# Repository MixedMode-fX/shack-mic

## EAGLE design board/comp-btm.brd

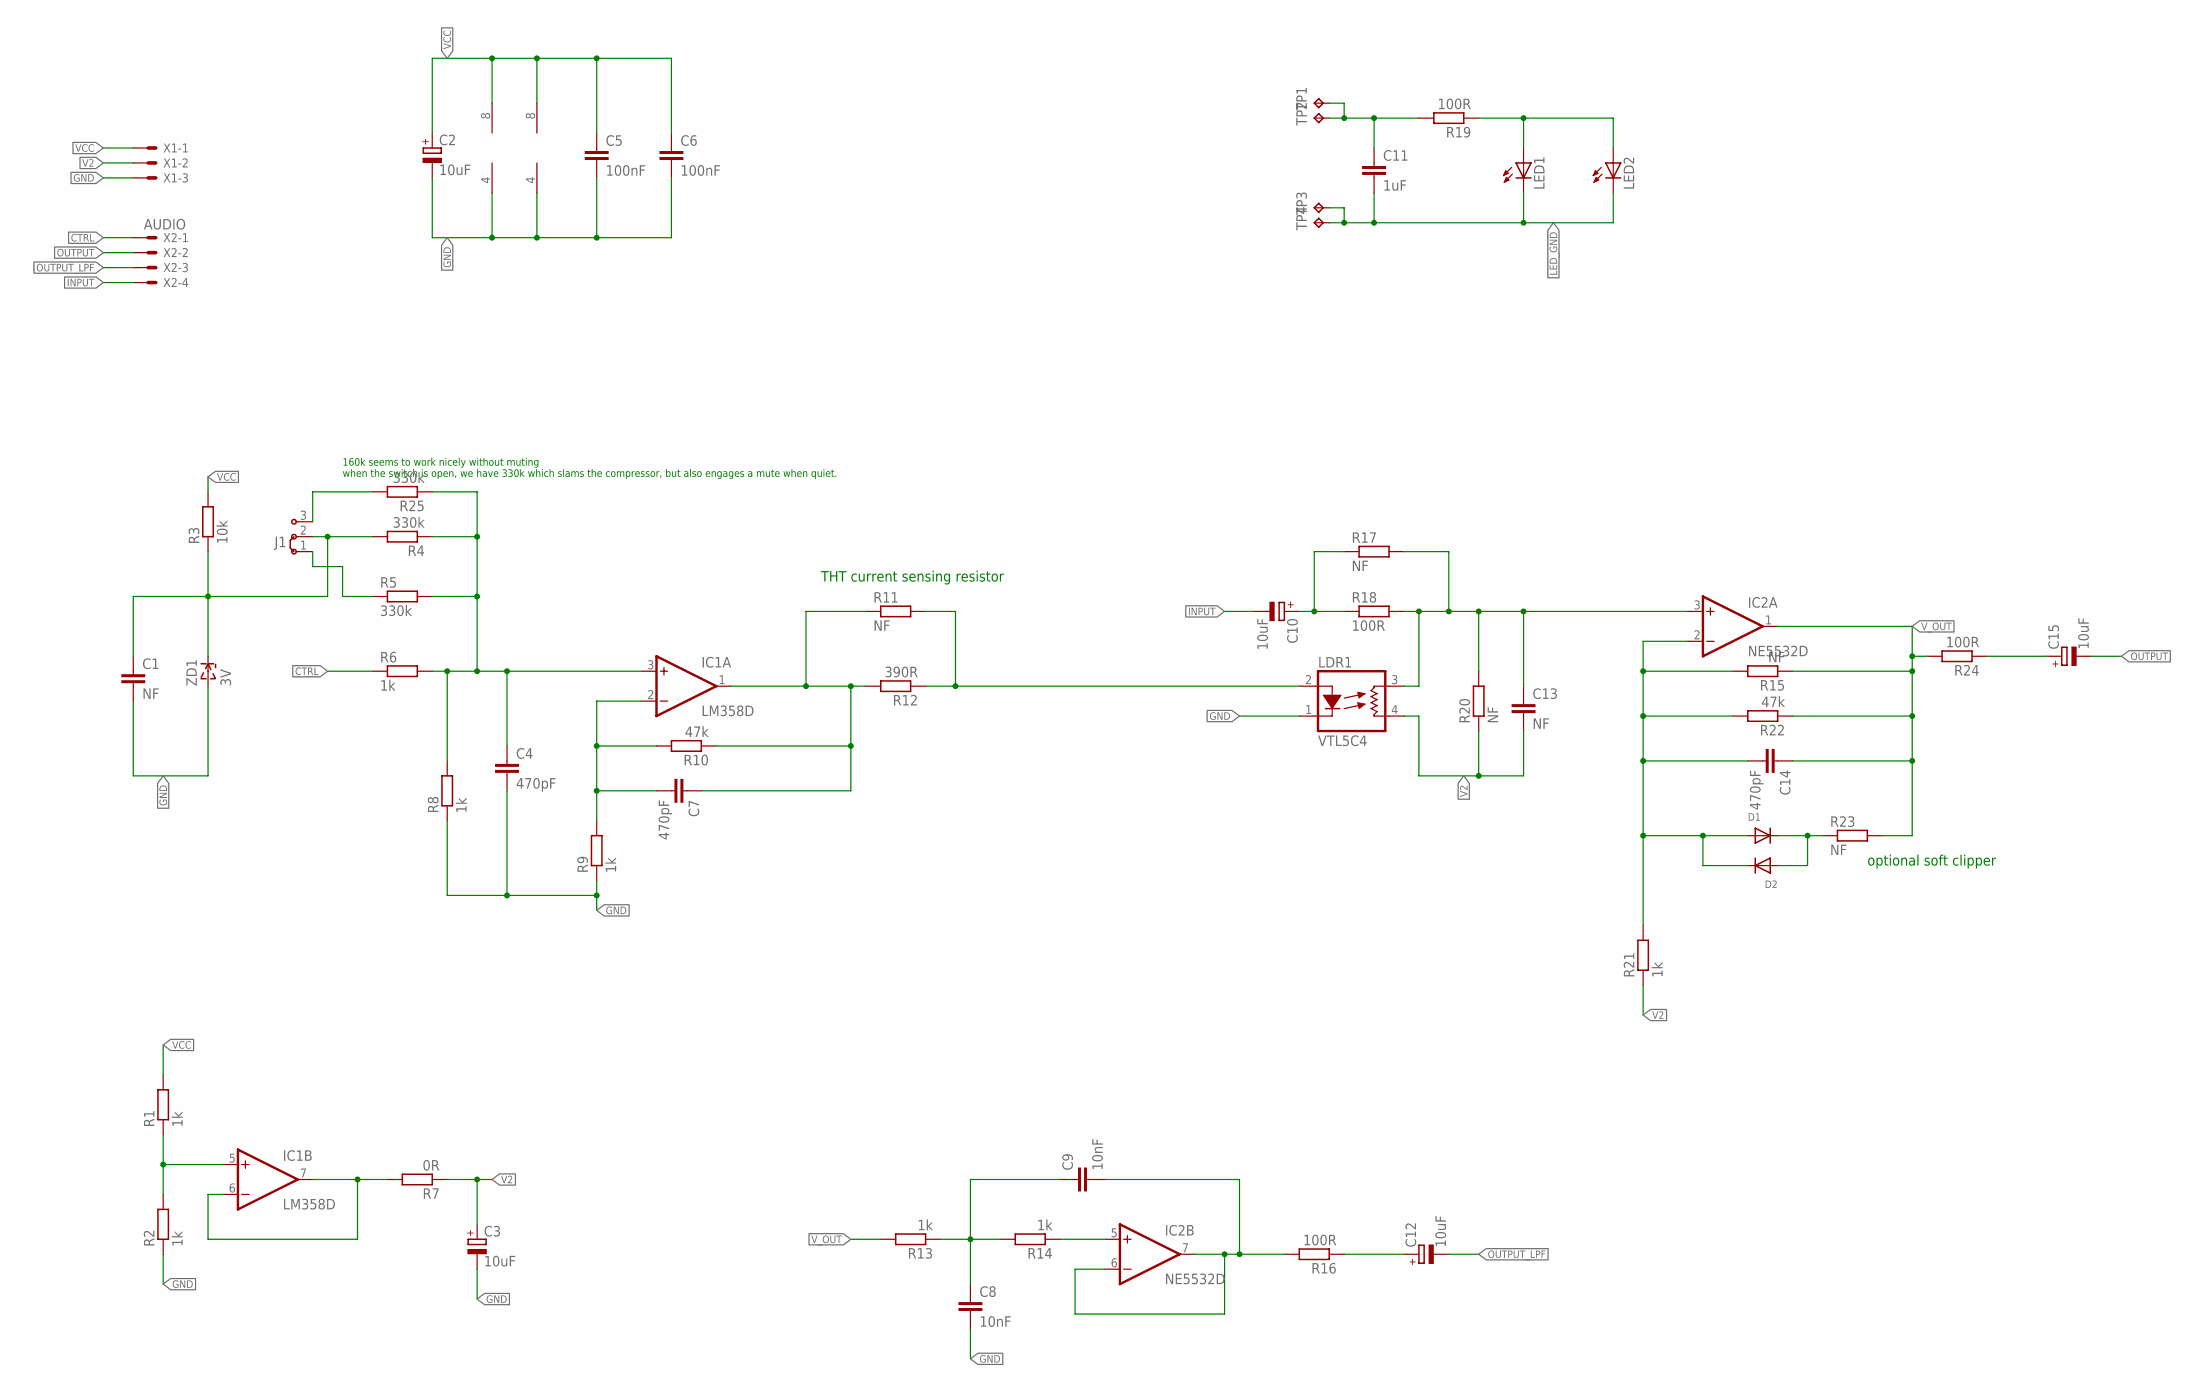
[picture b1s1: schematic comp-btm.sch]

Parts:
C1, C13: NF; C0805
C2, C3, C10, C12, C15: 10uF; E2,5-6E
C4, C7, C14: 470pF; C0805
C5, C6: 100nF; C0805
C8, C9: 10nF; C0805
C11: 1uF; C0805
D1, D2: DIODEDO-1N4148; DO-1N4148
IC1: LM358D; SO08
IC2: NE5532D; SO08
J1: J2X2MM; 04C
LDR1: VTL5C4; VTL5C
LED1, LED2: LEDCHIPLED_1206; CHIPLED_1206
R1, R2, R6, R8, R9, R13, R14, R21: 1k; R0805
R3: 10k; R0805
R4, R5, R25: 330k; R0805
R7: 0R; R0805
R10, R22: 47k; R0805
R11, R15, R17, R23: NF; 0309V
R12: 390R; R0805
R16, R18, R19, R24: 100R; R0805
R20: NF; R0805
TP1: +; TP20SQ
TP2, TP3, TP4: TPTP20SQ; TP20SQ
X1: POWER; JST-XH-03-PACKAGE-LONG-PAD
X2: AUDIO; JST-XH-04-PACKAGE-LONG-PAD
ZD1: 3V; SOD-123

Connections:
CTRL: R6.1, X2.1
GND: C1.2, C2.-, C3.-, C4.2, C5.2, C6.2, C8.2, IC1.4 (V-), IC2.4 (V-), LDR1.1 (C), R2.1, R8.1, R9.1, X1.3, ZD1.A
INPUT: C10.-, X2.4
LED_GND: C11.2, LED1.C, LED2.C, TP3.TP, TP4.TP
unnamed: IC1.5 (+IN), R1.1, R2.2
unnamed: C7.2, IC1.2 (-IN), R9.2, R10.2
unnamed: J1.1, R5.1
unnamed: C14.2, D1.A, D2.C, IC2.2 (-IN), R15.2, R21.2, R22.2
unnamed: C12.+, R16.1
unnamed: C7.1, IC1.1 (OUT), R10.1, R11.1, R12.2
unnamed: C13.1, IC2.3 (+IN), LDR1.3 (L1), R17.2, R18.2, R20.2
unnamed: C10.+, R17.1, R18.1
unnamed: C1.1, J1.2, R3.1, R4.2, ZD1.C
unnamed: LDR1.2 (A), R11.2, R12.1
unnamed: C8.1, C9.1, R13.1, R14.2
unnamed: C4.1, IC1.3 (+IN), R4.1, R5.2, R6.2, R8.2, R25.1
unnamed: C15.+, R24.1
unnamed: IC1.6 (-IN), IC1.7 (OUT), R7.2
unnamed: J1.3, R25.2
unnamed: C9.2, IC2.6 (-IN), IC2.7 (OUT), R16.2
unnamed: LED1.A, LED2.A, R19.1
unnamed: D1.C, D2.A, R23.1
unnamed: C11.1, R19.2, TP1.TP, TP2.TP
unnamed: IC2.5 (+IN), R14.1
OUTPUT: C15.-, X2.2
OUTPUT_LPF: C12.-, X2.3
V2: C3.+, C13.2, LDR1.4 (L2), R7.1, R20.1, R21.1, X1.2
VCC: C2.+, C5.1, C6.1, IC1.8 (V+), IC2.8 (V+), R1.2, R3.2, X1.1
V_OUT: C14.1, IC2.1 (OUT), R13.2, R15.1, R22.1, R23.2, R24.2

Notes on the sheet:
THT current sensing resistor
optional soft clipper
160k seems to work nicely without muting when the switch is open, we have 330k which slams the compressor, but also engages a mute when quiet.

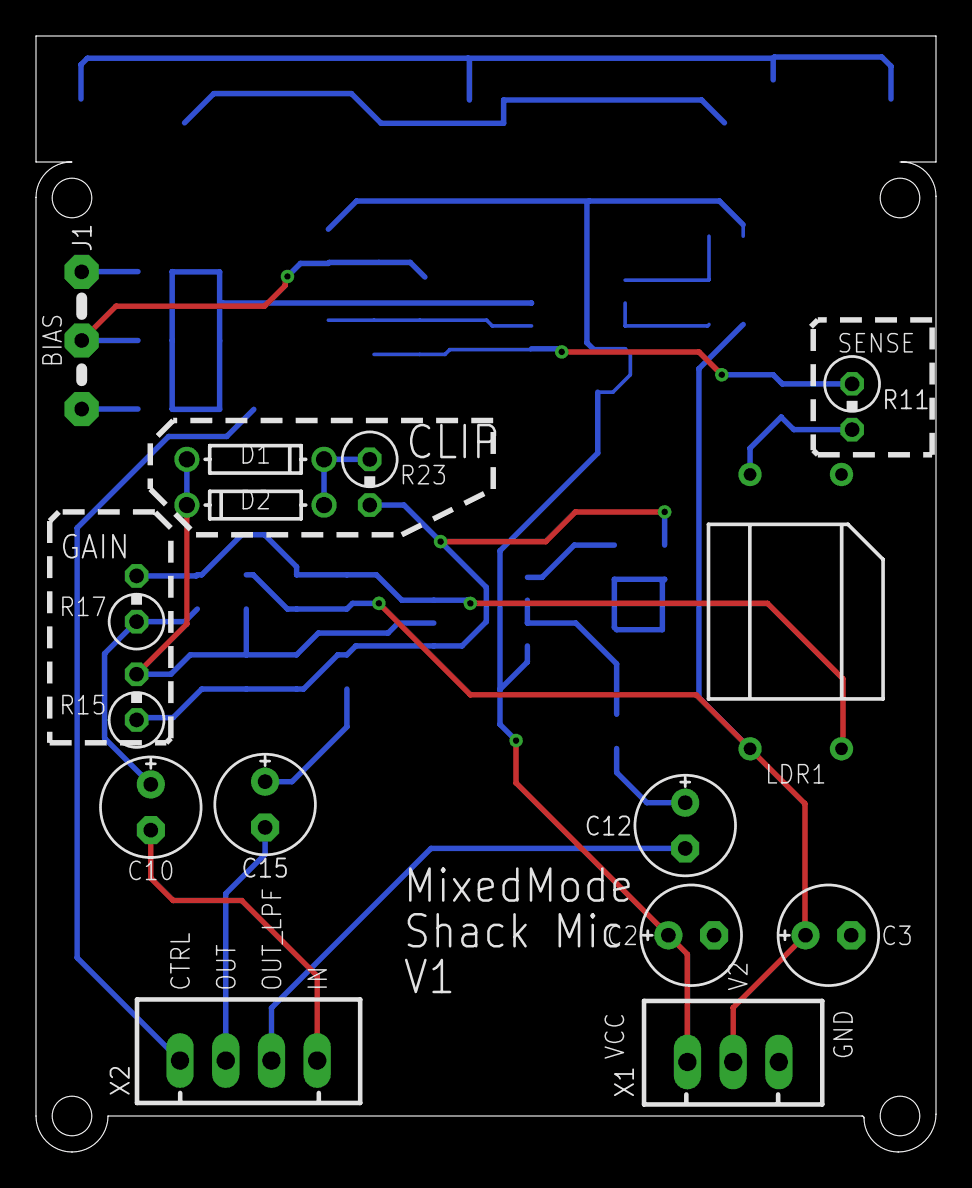
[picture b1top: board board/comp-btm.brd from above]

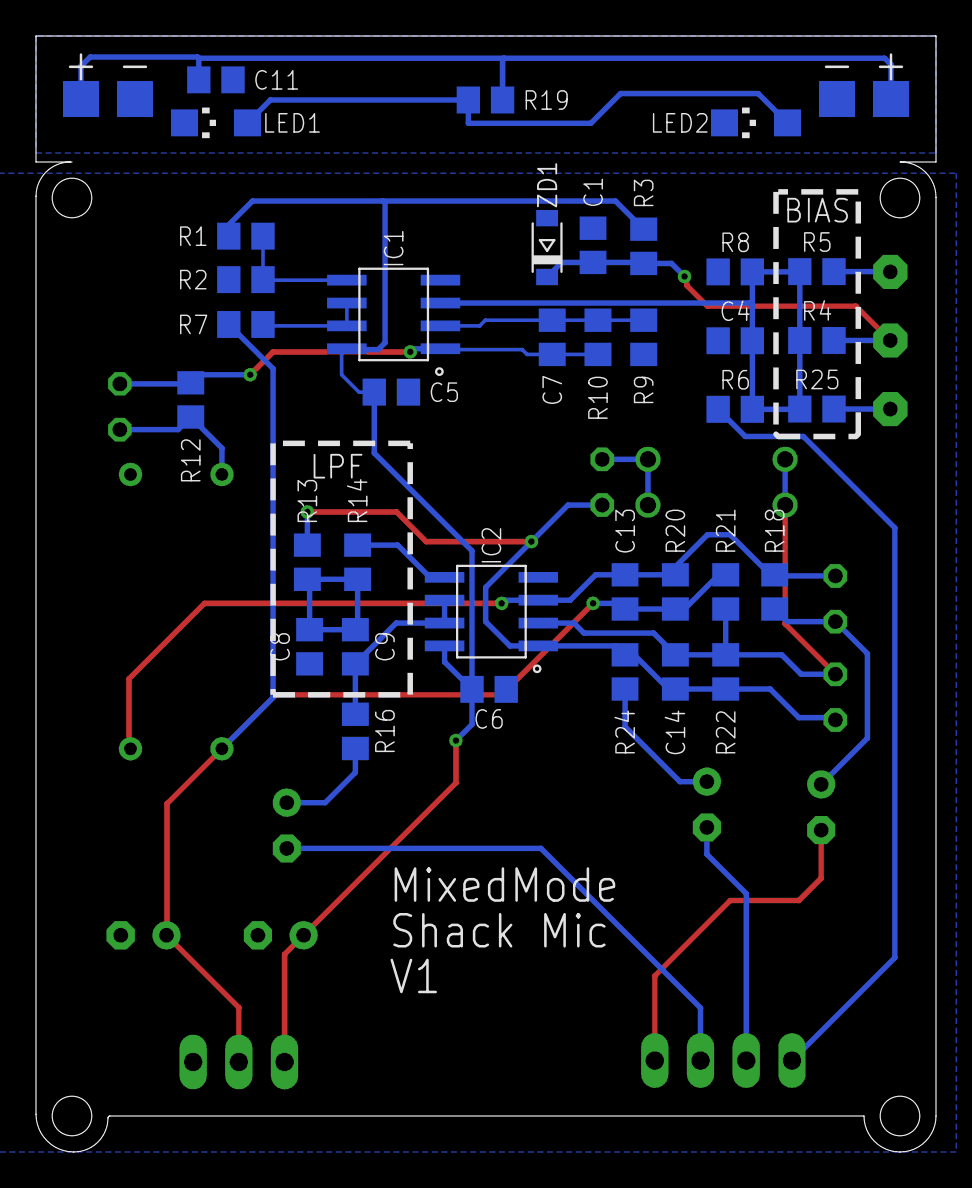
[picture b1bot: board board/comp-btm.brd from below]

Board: 2 copper layers, 50.0 x 62.0 mm, 55 parts (40 on the bottom side), 29 nets.

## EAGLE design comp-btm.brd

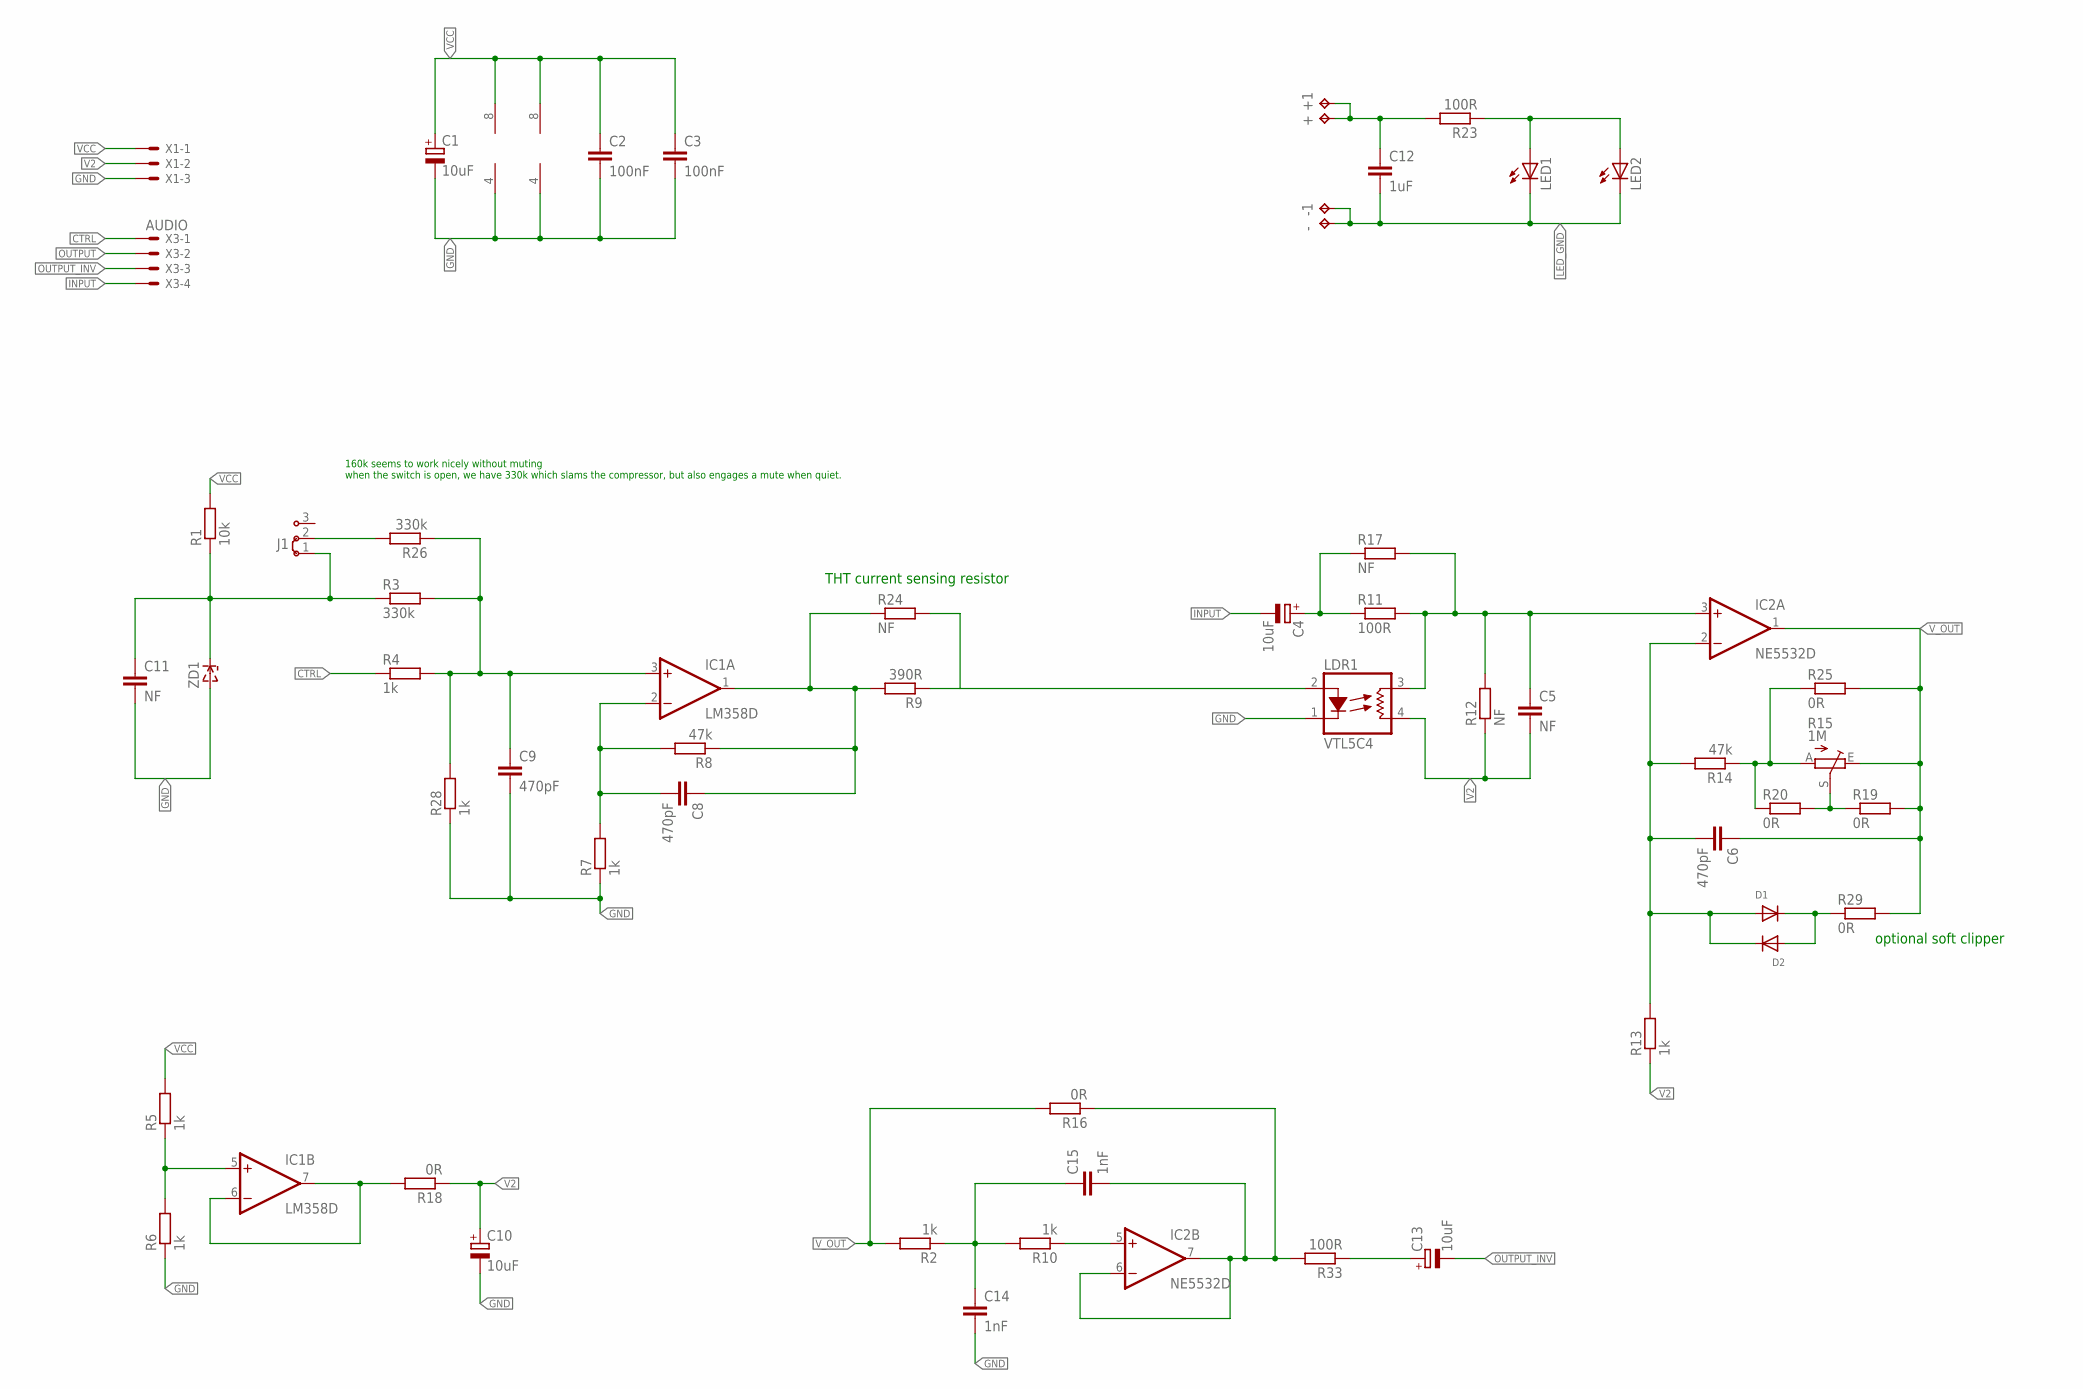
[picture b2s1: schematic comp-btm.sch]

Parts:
+: TPTP20SQ; TP20SQ
+1: +; TP20SQ
-, -1: TPTP20SQ; TP20SQ
C1, C4, C10, C13: 10uF; E3,5-8
C2, C3: 100nF; C0805
C5, C11: NF; C0805
C6, C8, C9: 470pF; C0805
C12: 1uF; C0805
C14, C15: 1nF; C0805
D1, D2: DIODEDO-1N4148; DO-1N4148
IC1: LM358D; SO08
IC2: NE5532D; SO08
J1: J2X2MM; 04C
LDR1: VTL5C4; VTL5C
LED1, LED2: LEDCHIPLED_1206; CHIPLED_1206
R1: 10k; R0805
R2, R4, R5, R6, R7, R10, R13, R28: 1k; R0805
R3, R26: 330k; R0805
R8, R14: 47k; R0805
R9: 390R; R0805
R11, R23, R33: 100R; R0805
R12: NF; R0805
R15: 1M; B64Y
R16, R18, R19, R20, R25, R29: 0R; R0805
R17, R24: NF; 0309V
X1: POWER; JST-XH-03-PACKAGE-LONG-PAD
X3: AUDIO; JST-XH-04-PACKAGE-LONG-PAD
ZD1: ZENERSOD-123; SOD-123

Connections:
CTRL: R4.1, X3.1
GND: C1.-, C2.2, C3.2, C9.2, C10.-, C11.2, C14.2, IC1.4 (V-), IC2.4 (V-), LDR1.1 (C), R6.1, R7.1, R28.1, X1.3, ZD1.A
INPUT: C4.-, X3.4
LED_GND: -.TP, -1.TP, C12.2, LED1.C, LED2.C
unnamed: IC1.5 (+IN), R5.1, R6.2
unnamed: C8.2, IC1.2 (-IN), R7.2, R8.2
unnamed: C9.1, IC1.3 (+IN), R3.2, R4.2, R26.1, R28.2
unnamed: C6.2, D1.A, D2.C, IC2.2 (-IN), R13.2, R14.2
unnamed: C13.+, R33.1
unnamed: C8.1, IC1.1 (OUT), R8.1, R9.2, R24.1
unnamed: C5.1, IC2.3 (+IN), LDR1.3 (L1), R11.2, R12.2, R17.2
unnamed: C4.+, R11.1, R17.1
unnamed: J1.2, R26.2
unnamed: LDR1.2 (A), R9.1, R24.2
unnamed: C14.1, C15.1, R2.1, R10.2
unnamed: R14.1, R15.A, R20.1, R25.1
unnamed: IC1.6 (-IN), IC1.7 (OUT), R18.2
unnamed: R15.S, R19.1, R20.2
unnamed: C15.2, IC2.6 (-IN), IC2.7 (OUT), R16.1, R33.2
unnamed: LED1.A, LED2.A, R23.1
unnamed: D1.C, D2.A, R29.1
unnamed: +.TP, +1.TP, C12.1, R23.2
unnamed: IC2.5 (+IN), R10.1
unnamed: C11.1, J1.1, R1.1, R3.1, ZD1.C
OUTPUT: X3.2
OUTPUT_INV: C13.-, X3.3
V2: C5.2, C10.+, LDR1.4 (L2), R12.1, R13.1, R18.1, X1.2
VCC: C1.+, C2.1, C3.1, IC1.8 (V+), IC2.8 (V+), R1.2, R5.2, X1.1
V_OUT: C6.1, IC2.1 (OUT), R2.2, R15.E, R16.2, R19.2, R25.2, R29.2

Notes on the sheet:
THT current sensing resistor
optional soft clipper
160k seems to work nicely without muting when the switch is open, we have 330k which slams the compressor, but also engages a mute when quiet.

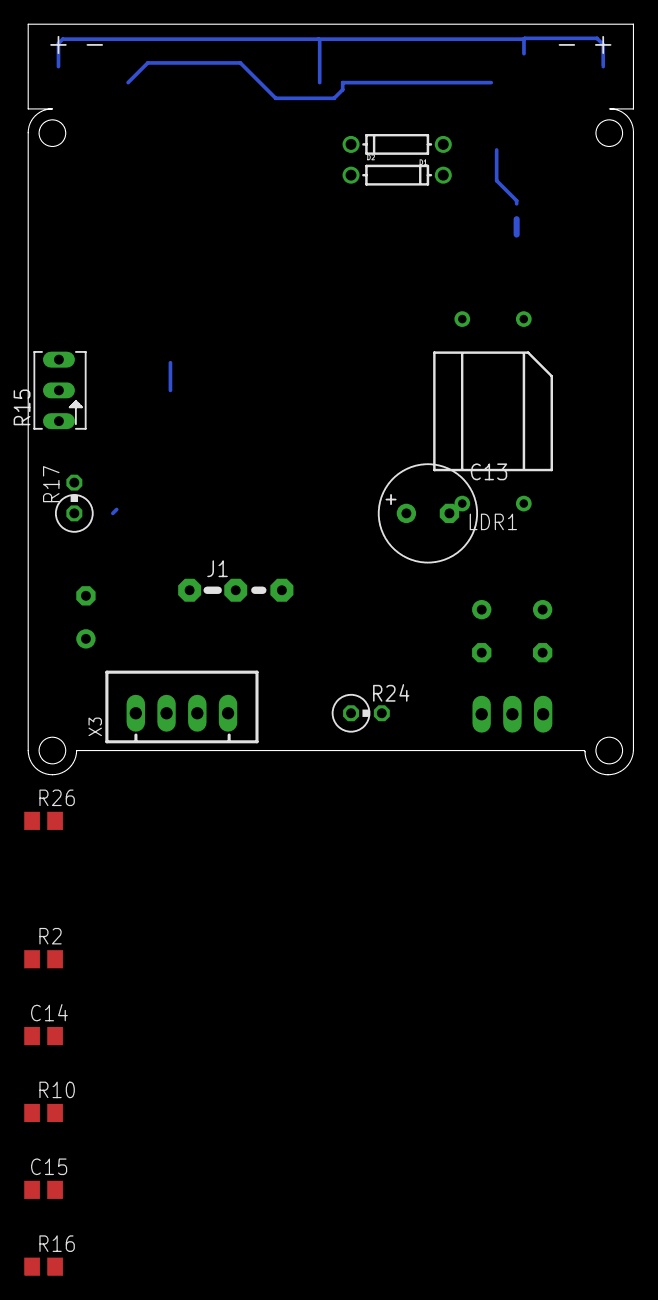
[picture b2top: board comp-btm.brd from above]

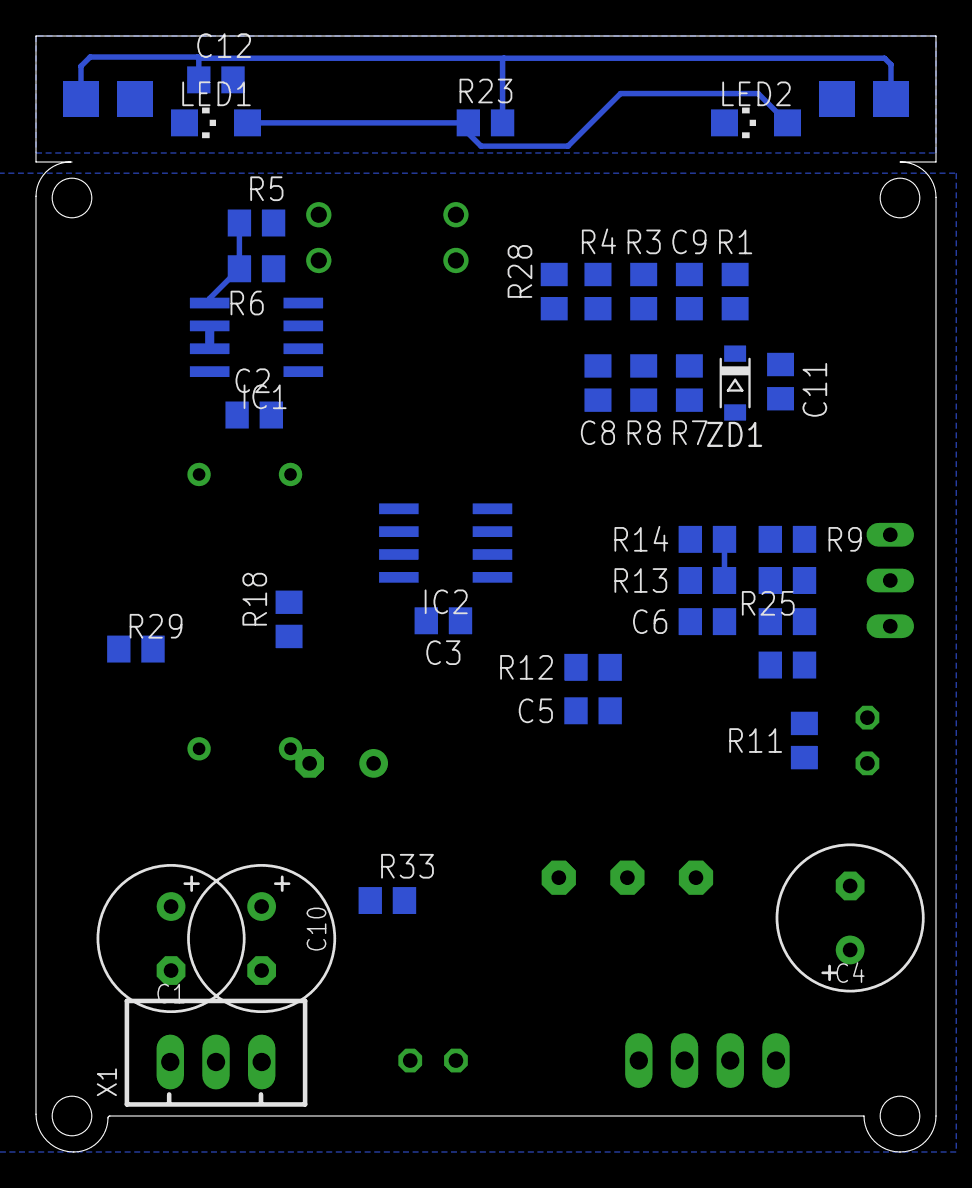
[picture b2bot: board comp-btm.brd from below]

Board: 2 copper layers, 50.0 x 62.0 mm, 56 parts (41 on the bottom side), 28 nets.

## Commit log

2020-09-12 schematic & reference layout
2021-01-24 V1 build
2021-02-20 calculation
